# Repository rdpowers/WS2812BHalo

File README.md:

WS2812B Halo
=============

This simple board features 24 WS2812B integrated LEDs and drivers arranged circularly. 

The interior cut may be resized or removed entirely to vary the disk. Watch your traces : )

Other circular arrangements may be calculated using the Positions.ods spreadsheet. Enjoy.

CREDITS
------------
This board was designed by Robert Powers - rdpowers@gmail.com - https://github.com/rdpowers

He's happy to hear from you if you've done something with this design that is novel, interesing, or if you wish to modify it in any way.

SPECIAL THANKS
------------
To the creators and maintainers of the KiCAD open-source EDA suite.
To the HackMelbourne (CCHS) community of Melbourne, Australia. Especially Andy Gelme, Lachlan Maher, and John Bosua.
To all other open-source developers whose countless hours supported every other aspect of this design.

DISTRIBUTION
------------
The specific terms of distribution of this project are governed by the
license referenced below. Please contact the copyright owner if you wish to modify the board for distribution. Please utilize this design for personal or research projects. Please acknowledge all contributors.

LICENSE
-------
Licensed under the TAPR Open Hardware License (www.tapr.org/OHL).
The "license" sub-folder also contains a copy of this license in plain text format.

Copyright Robert Powers 2013
rdpowers@gmail.com

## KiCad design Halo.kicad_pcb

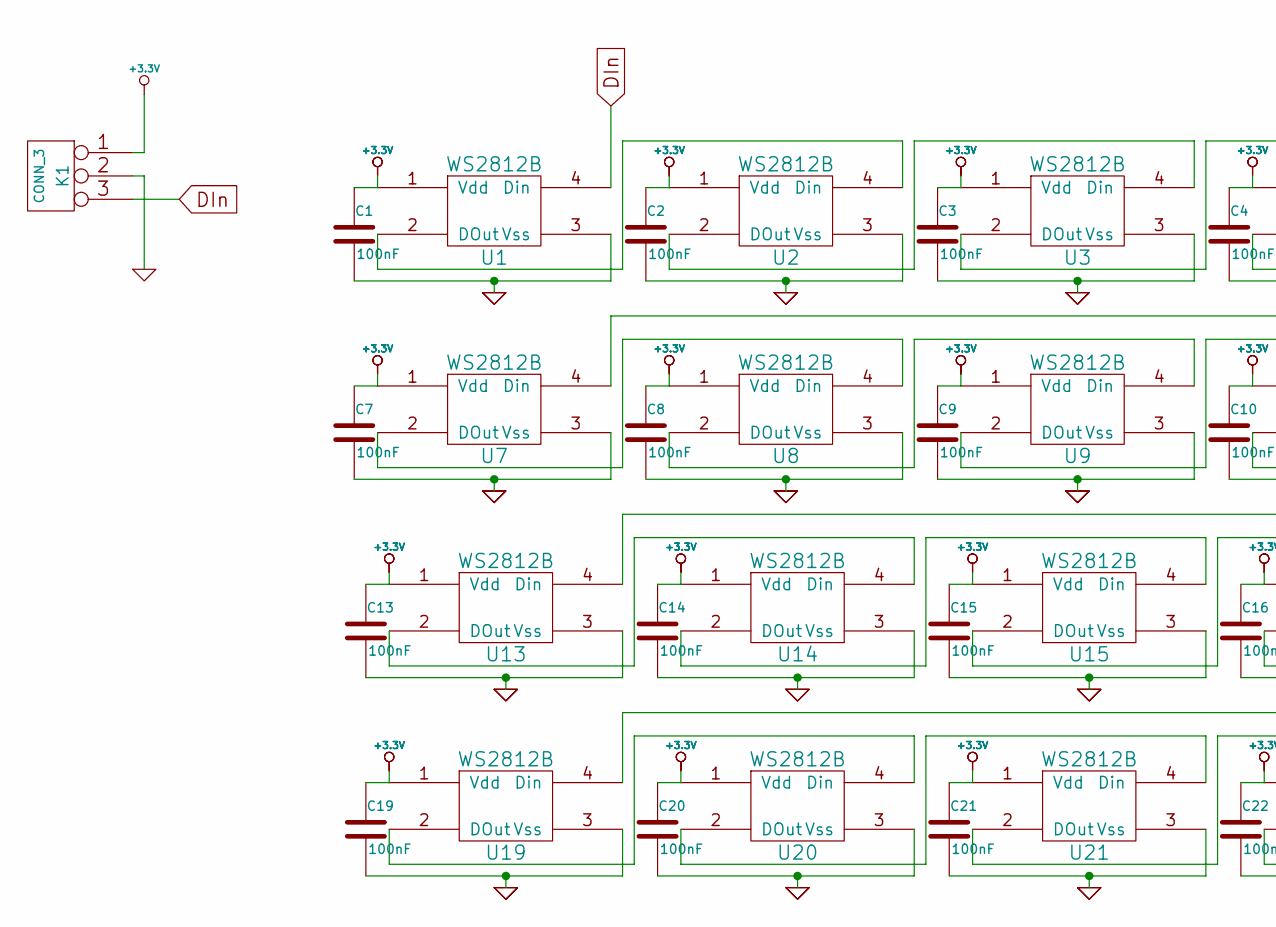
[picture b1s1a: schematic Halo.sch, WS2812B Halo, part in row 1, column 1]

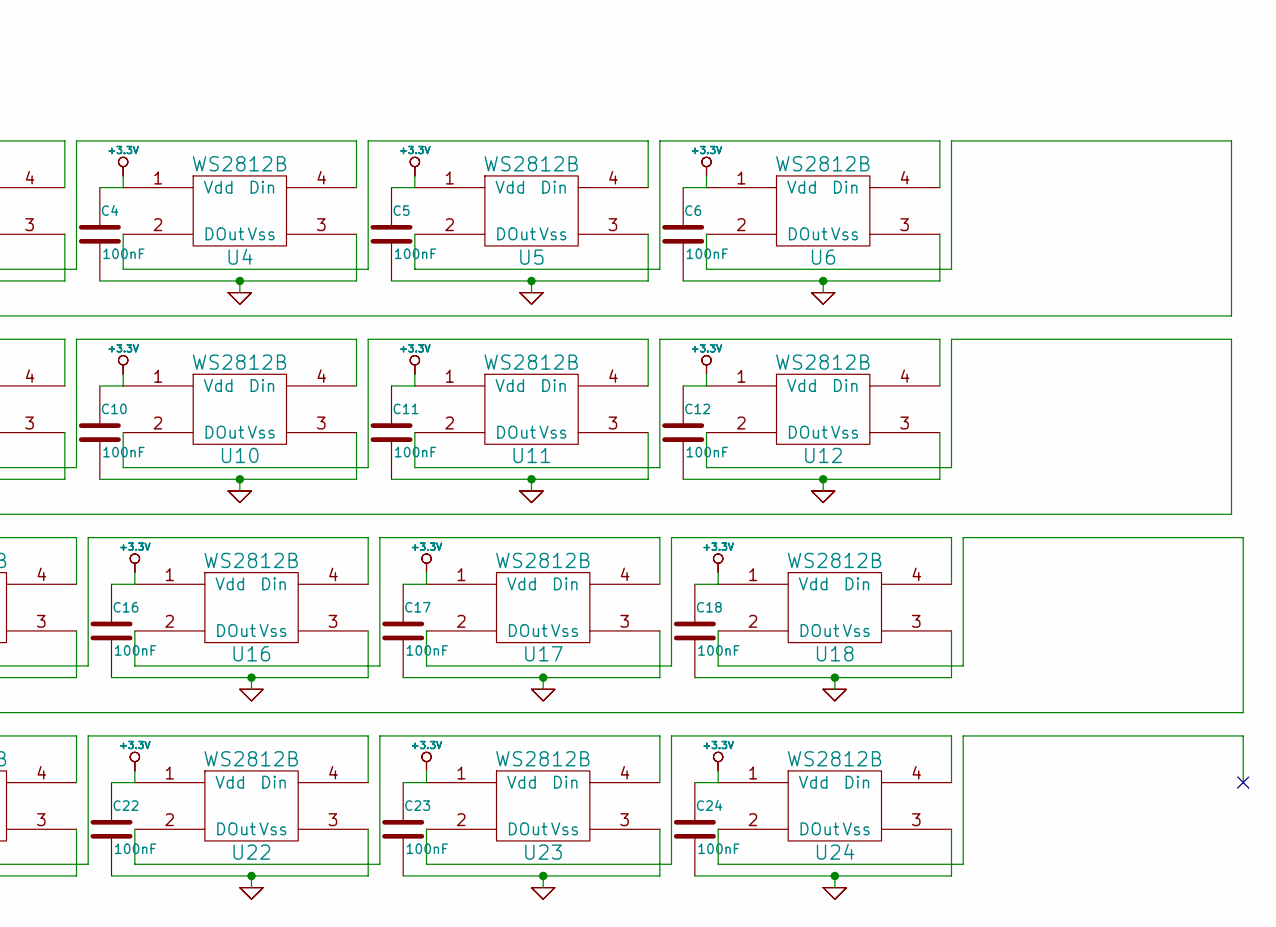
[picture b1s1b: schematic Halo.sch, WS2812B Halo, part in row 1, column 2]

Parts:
C1, C2, C3, C4, C5, C6, C7, C8, C9, C10, C11, C12, C13, C14, C15, C16, C17, C18, C19, C20, C21, C22, C23, C24: 100nF
K1: CONN_3
U1, U2, U3, U4, U5, U6, U7, U8, U9, U10, U11, U12, U13, U14, U15, U16, U17, U18, U19, U20, U21, U22, U23, U24: WS2812B

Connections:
+3.3V: C1.1, C2.1, C3.1, C4.1, C5.1, C6.1, C7.1, C8.1, C9.1, C10.1, C11.1, C12.1, C13.1, C14.1, C15.1, C16.1, C17.1, C18.1, C19.1, C20.1, C21.1, C22.1, C23.1, C24.1, K1.1, U1.1 (Vdd), U2.1 (Vdd), U3.1 (Vdd), U4.1 (Vdd), U5.1 (Vdd), U6.1 (Vdd), U7.1 (Vdd), U8.1 (Vdd), U9.1 (Vdd), U10.1 (Vdd), U11.1 (Vdd), U12.1 (Vdd), U13.1 (Vdd), U14.1 (Vdd), U15.1 (Vdd), U16.1 (Vdd), U17.1 (Vdd), U18.1 (Vdd), U19.1 (Vdd), U20.1 (Vdd), U21.1 (Vdd), U22.1 (Vdd), U23.1 (Vdd), U24.1 (Vdd)
DIn: K1.3, U1.4 (Din)
GND: C1.2, C2.2, C3.2, C4.2, C5.2, C6.2, C7.2, C8.2, C9.2, C10.2, C11.2, C12.2, C13.2, C14.2, C15.2, C16.2, C17.2, C18.2, C19.2, C20.2, C21.2, C22.2, C23.2, C24.2, K1.2 (PM), U1.3 (Vss), U2.3 (Vss), U3.3 (Vss), U4.3 (Vss), U5.3 (Vss), U6.3 (Vss), U7.3 (Vss), U8.3 (Vss), U9.3 (Vss), U10.3 (Vss), U11.3 (Vss), U12.3 (Vss), U13.3 (Vss), U14.3 (Vss), U15.3 (Vss), U16.3 (Vss), U17.3 (Vss), U18.3 (Vss), U19.3 (Vss), U20.3 (Vss), U21.3 (Vss), U22.3 (Vss), U23.3 (Vss), U24.3 (Vss)
unnamed: U16.2 (DOut), U17.4 (Din)
unnamed: U15.2 (DOut), U16.4 (Din)
unnamed: U18.2 (DOut), U19.4 (Din)
unnamed: U17.2 (DOut), U18.4 (Din)
unnamed: U13.2 (DOut), U14.4 (Din)
unnamed: U14.2 (DOut), U15.4 (Din)
unnamed: U22.2 (DOut), U23.4 (Din)
unnamed: U21.2 (DOut), U22.4 (Din)
unnamed: U23.2 (DOut), U24.4 (Din)
unnamed: U6.2 (DOut), U7.4 (Din)
unnamed: U19.2 (DOut), U20.4 (Din)
unnamed: U20.2 (DOut), U21.4 (Din)
unnamed: U4.2 (DOut), U5.4 (Din)
unnamed: U3.2 (DOut), U4.4 (Din)
unnamed: U5.2 (DOut), U6.4 (Din)
unnamed: U2.2 (DOut), U3.4 (Din)
unnamed: U1.2 (DOut), U2.4 (Din)
unnamed: U9.2 (DOut), U10.4 (Din)
unnamed: U10.2 (DOut), U11.4 (Din)
unnamed: U12.2 (DOut), U13.4 (Din)
unnamed: U11.2 (DOut), U12.4 (Din)
unnamed: U7.2 (DOut), U8.4 (Din)
unnamed: U8.2 (DOut), U9.4 (Din)

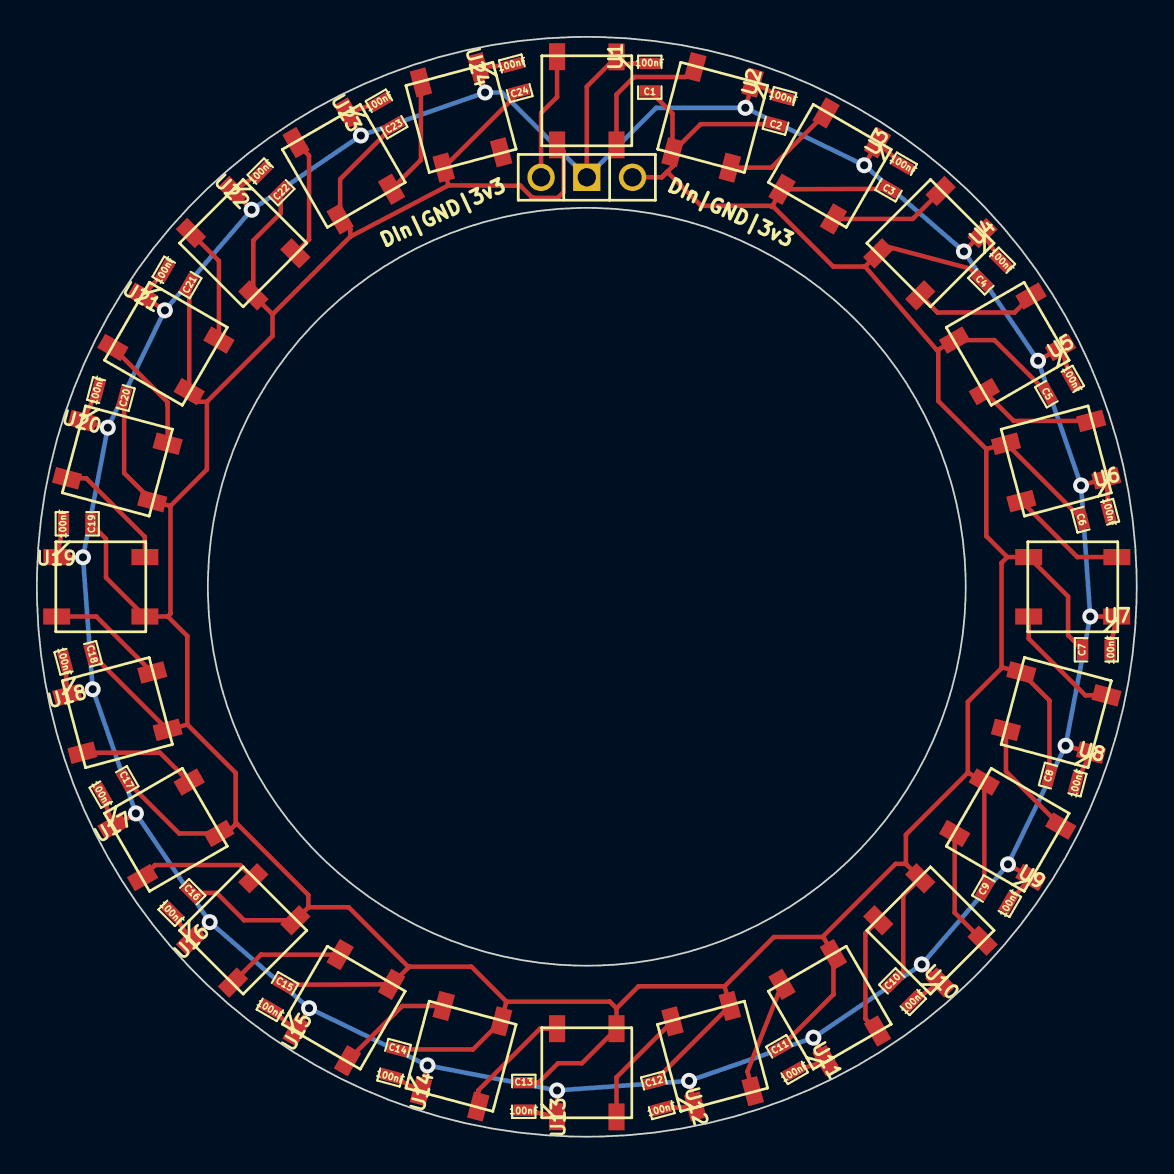
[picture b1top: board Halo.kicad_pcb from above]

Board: 2 copper layers, 61.1 x 61.1 mm, 49 parts (0 on the bottom side), 26 nets.

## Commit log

2013-10-12 Halo commit\!
2013-10-25 Markdown.

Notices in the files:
Halo.kicad_pcb:
© Bob Powers 2013
